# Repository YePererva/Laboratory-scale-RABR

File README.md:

# Laboratory scale RABR

This repository contains some developments on laboratory-scale Rotating Algal Biofilm Reactor (RABR).
The reactor were build for one of student-projects.

# Content

Folder `electronics` contains the schematics for two designed devices:
- Motor controller for there stepper motors as shaft drives for reactor
- Environment monitor for monitoring conditions of air and light around reactor. This monitor reads:
   - Temperature, Pressure and Relative Humidity of air (with conversion to absolute humidity)
   - Total flux, Photo-synthetically Active Radiation, UV flux.

Folder `models` contains the designer reactor for running in triplicate.

Folder `images` contains CAD renders and photos taken of working reactor and equipment.

# Used tools:
- KiCad : for schematics
- SolidWorks Educational : for designing the reactor

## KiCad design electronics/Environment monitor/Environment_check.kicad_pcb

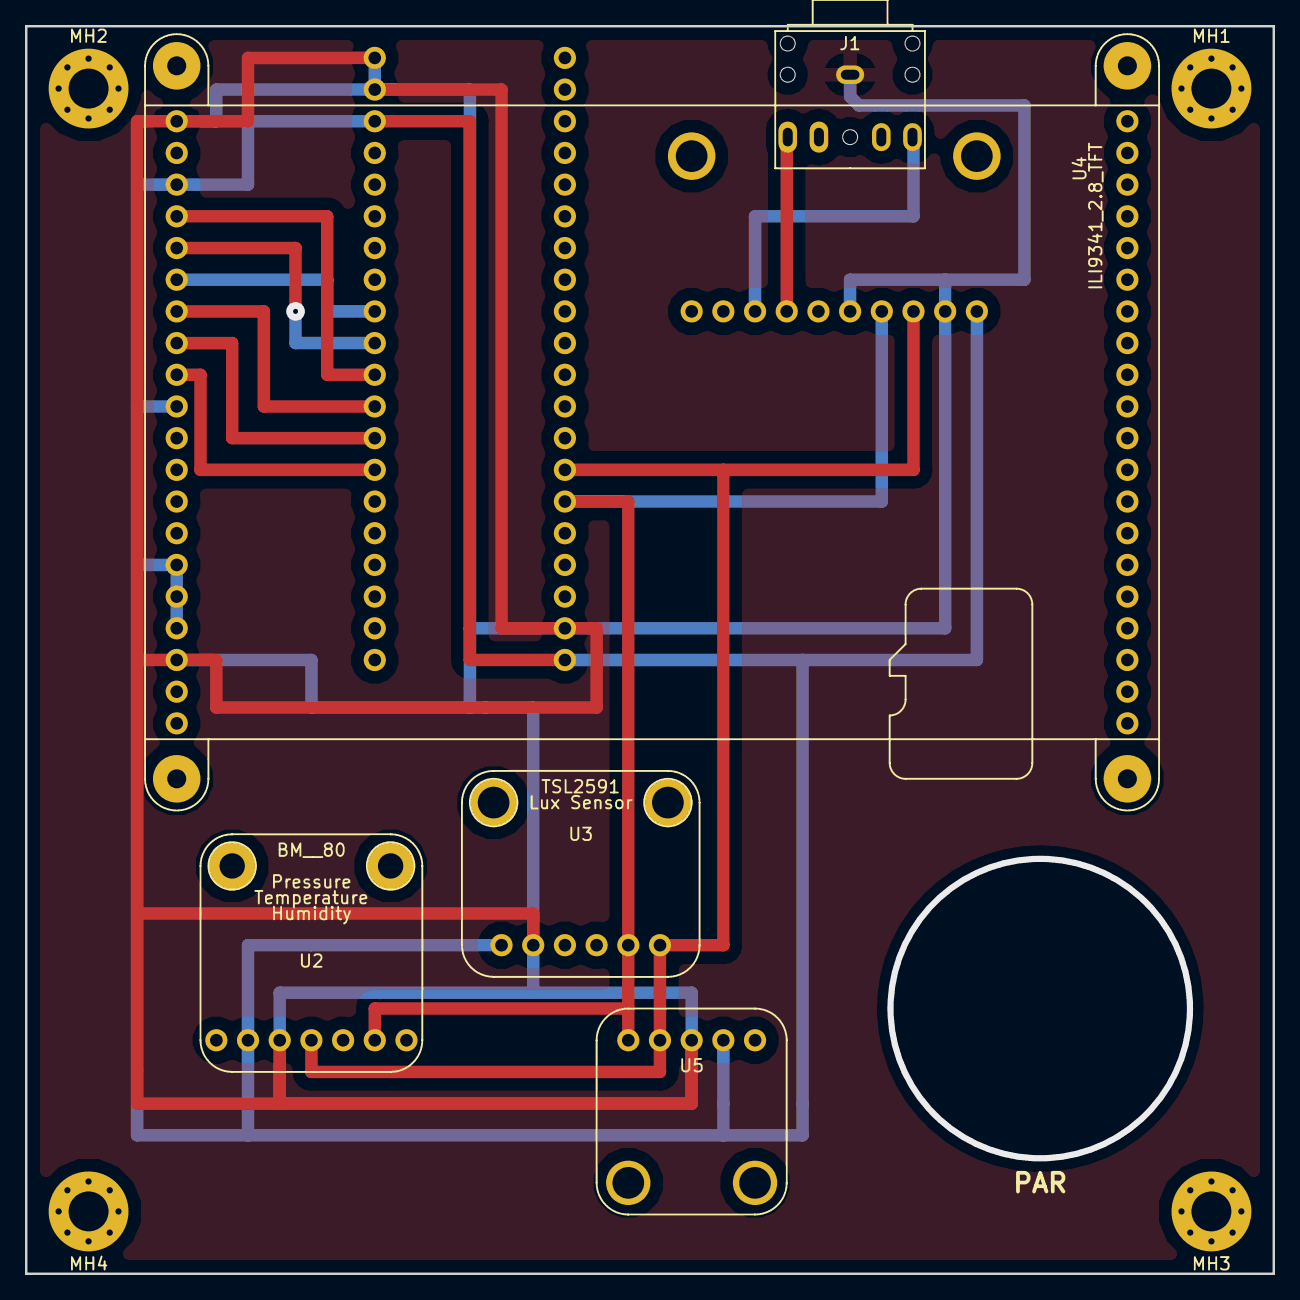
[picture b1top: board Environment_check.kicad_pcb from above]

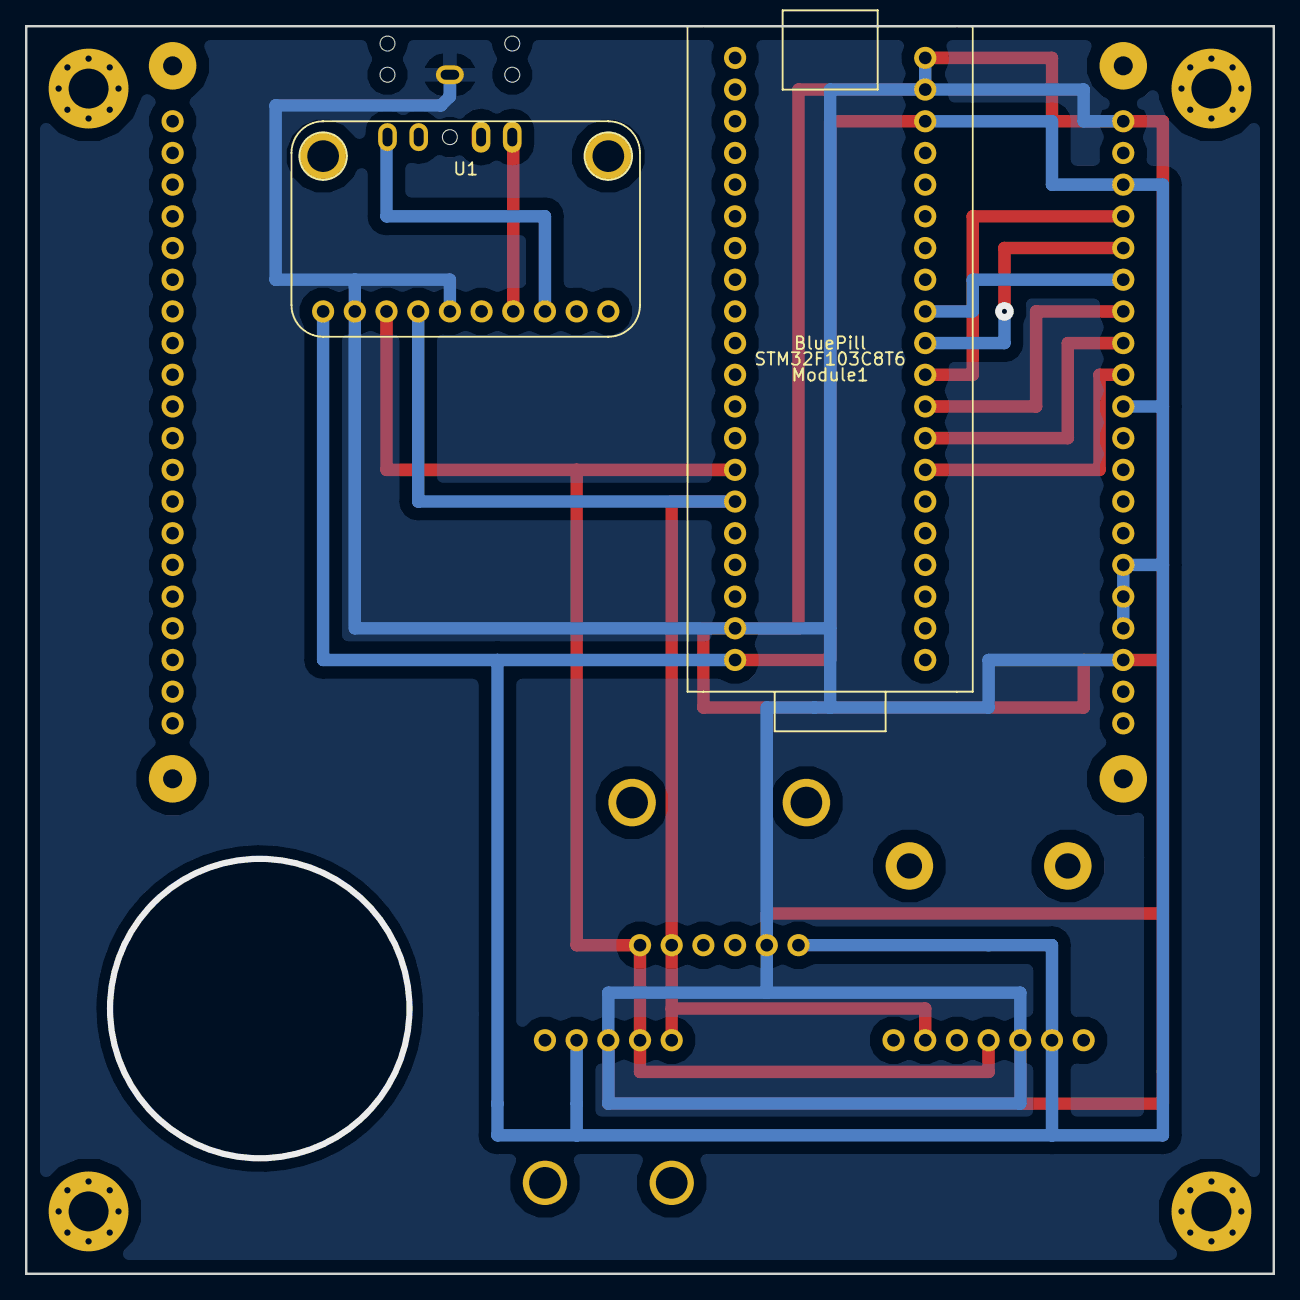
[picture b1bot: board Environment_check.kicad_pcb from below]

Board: 2 copper layers, 100.0 x 100.0 mm, 11 parts (2 on the bottom side), 12 nets.

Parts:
J1: Audio_3.5mm; Audio 3.5 Jack [4Ucon 08780]
MH1, MH2, MH3, MH4: MountingHole; MountingHole_3.2mm_M3_Pad_Via
Module1: BluePill
U1: ADS1115_ADS1015
U2: BM__80; BME280_BMP280_BME680
U3: TSL2591
U4: ILI9341_2.8_TFT; adafruit_ILI9341_2.8_double_mode
U5: VEML6075

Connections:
+3V3: Module1.20, Module1.38, U1.1, U2.2, U3.1, U4.23, U4.30, U4.35, U4.36, U4.37, U5.2
CLK: Module1.30, U4.24
ChipSelect: Module1.29, U4.27
Data_Command: Module1.28, U4.28
GND: J1.1, Module1.19, Module1.39, Module1.40, U1.2, U1.5, U2.3, U3.2, U4.21, U4.38, U5.3
MISO: Module1.31, U4.25
MOSI: Module1.32, U4.26
unnamed: J1.2, U1.8
unnamed: J1.5, U1.7
Reset: Module1.27, U4.29
SCL: Module1.14, U1.3, U2.4, U3.6, U5.4
SDA: Module1.15, U1.4, U2.6, U3.5, U5.5

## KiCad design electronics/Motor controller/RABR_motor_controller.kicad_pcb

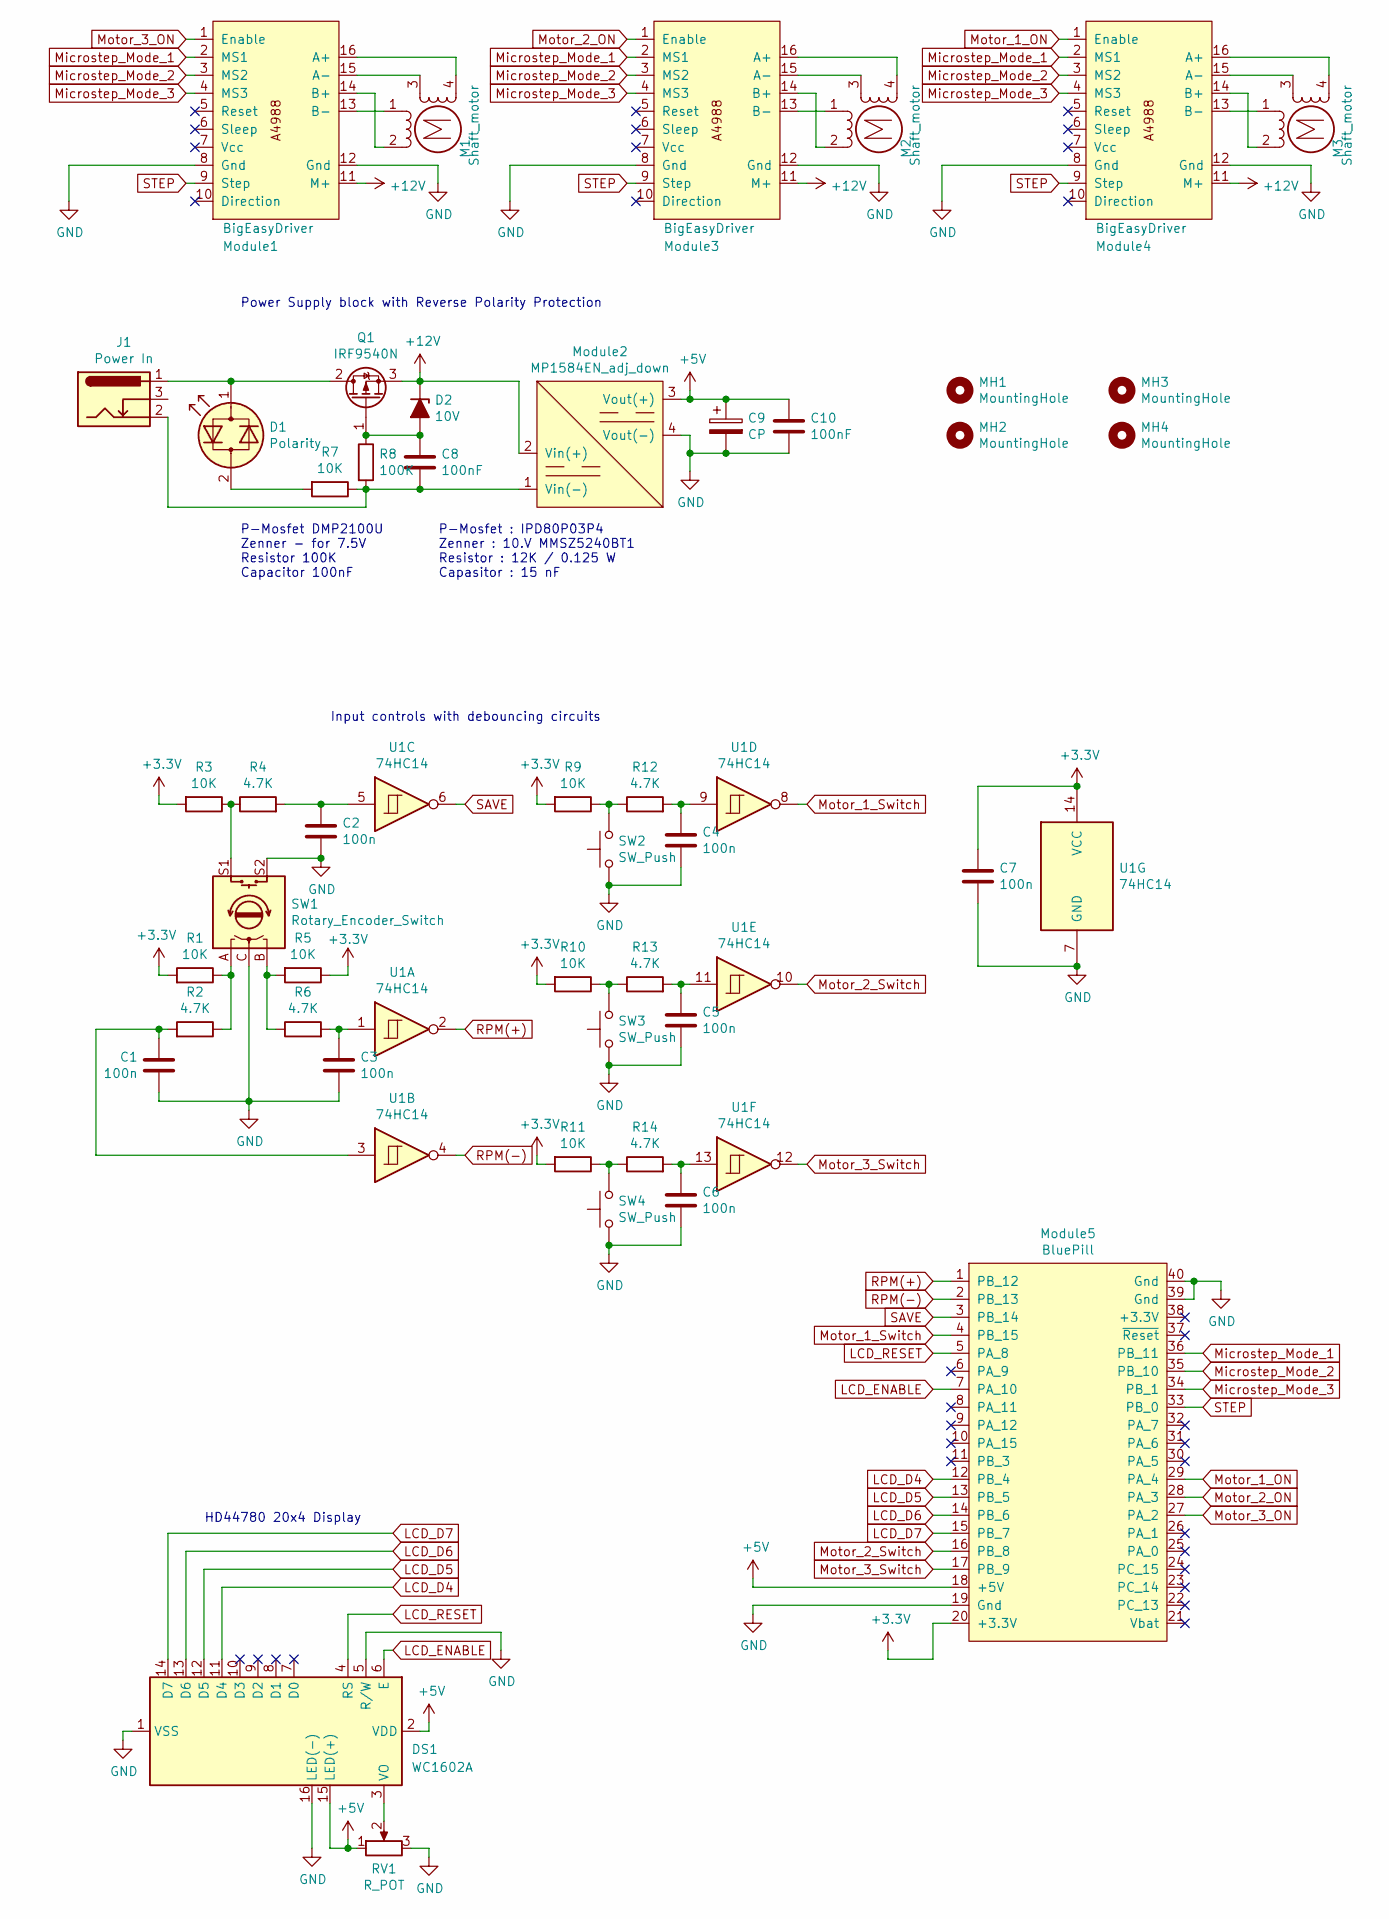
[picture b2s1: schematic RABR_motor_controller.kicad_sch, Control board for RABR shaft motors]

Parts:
C1, C2, C3, C4, C5, C6, C7: 100n; C_0805_2012Metric_Pad1.15x1.40mm_HandSolder
C8, C10: 100nF; C_0805_2012Metric_Pad1.15x1.40mm_HandSolder
C9: CP; CP_Elec_10x10
D1: Polarity; LED_D3.0mm_Clear
D2: 10V; D_DO-41_SOD81_P7.62mm_Horizontal
DS1: WC1602A
J1: Power In; BarrelJack_Horizontal
M1, M2, M3: Shaft_motor; TerminalBlock_Phoenix_MPT-0,5-4-2.54_1x04_P2.54mm_Horizontal
MH1, MH2, MH3, MH4: MountingHole; MountingHole_3.2mm_M3_DIN965_Pad
Module1, Module3, Module4: BigEasyDriver; BigEasyDriver_v1.6
Module2: MP1584EN_adj_down; MP1584_adj
Module5: BluePill
Q1: IRF9540N; TO-220-3_Vertical
R1, R3, R5, R7, R9, R10, R11: 10K; R_1206_3216Metric_Pad1.42x1.75mm_HandSolder
R2, R4, R6, R12, R13, R14: 4.7K; R_1206_3216Metric_Pad1.42x1.75mm_HandSolder
R8: 100K; R_1206_3216Metric_Pad1.42x1.75mm_HandSolder
RV1: R_POT; Potentiometer_Bourns_3386C_Horizontal
SW1: Rotary_Encoder_Switch; RotaryEncoder_Alps_EC12E-Switch_Vertical_H20mm
SW2, SW3, SW4: SW_Push; SW_PUSH_6mm_H8.5mm
U1: 74HC14; DIP-14_W7.62mm_LongPads

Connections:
+3V3: C7.1, Module5.20 (+3.3V), R1.2, R3.2, R5.1, R9.2, R10.2, R11.2, U1.14 (VCC)
+5V: C9.1, C10.1, DS1.2 (VDD), DS1.15 (LED(+)), Module2.3 (Vout(+)), Module5.18 (+5V), RV1.1
+12V: D2.1 (K), Module1.11 (M+), Module2.2 (Vin(+)), Module3.11 (M+), Module4.11 (M+), Q1.3 (S)
GND: C1.2, C2.2, C3.2, C4.2, C5.2, C6.2, C7.2, C9.2, C10.2, DS1.1 (VSS), DS1.5 (R/W), DS1.16 (LED(-)), Module1.8 (Gnd), Module1.12 (Gnd), Module2.4 (Vout(-)), Module3.8 (Gnd), Module3.12 (Gnd), Module4.8 (Gnd), Module4.12 (Gnd), Module5.19 (Gnd), Module5.39 (Gnd), Module5.40 (Gnd), RV1.3, SW1.C, SW1.S2, SW2.1, SW3.1, SW4.1, U1.7 (GND)
LCD_D4: DS1.11 (D4), Module5.12 (PB_4)
LCD_D5: DS1.12 (D5), Module5.13 (PB_5)
LCD_D6: DS1.13 (D6), Module5.14 (PB_6)
LCD_D7: DS1.14 (D7), Module5.15 (PB_7)
LCD_ENABLE: DS1.6 (E), Module5.7 (PA_10)
LCD_RESET: DS1.4 (RS), Module5.5 (PA_8)
Microstep_Mode_1: Module1.2 (MS1), Module3.2 (MS1), Module4.2 (MS1), Module5.36 (PB_11)
Microstep_Mode_2: Module1.3 (MS2), Module3.3 (MS2), Module4.3 (MS2), Module5.35 (PB_10)
Microstep_Mode_3: Module1.4 (MS3), Module3.4 (MS3), Module4.4 (MS3), Module5.34 (PB_1)
Motor_1_ON: Module4.1 (Enable), Module5.29 (PA_4)
Motor_1_Switch: Module5.4 (PB_15), U1.8
Motor_2_ON: Module3.1 (Enable), Module5.28 (PA_3)
Motor_2_Switch: Module5.16 (PB_8), U1.10
Motor_3_ON: Module1.1 (Enable), Module5.27 (PA_2)
Motor_3_Switch: Module5.17 (PB_9), U1.12
unnamed: C1.1, R2.2, U1.3
unnamed: C2.1, R4.2, U1.5
unnamed: C3.1, R6.2, U1.1
unnamed: C4.1, R12.2, U1.9
unnamed: C5.1, R13.2, U1.11
unnamed: C6.1, R14.2, U1.13
unnamed: C8.1, D2.2 (A), Q1.1 (G), R8.1
unnamed: C8.2, J1.2, Module2.1 (Vin(-)), R7.1, R8.2
unnamed: D1.1 (KA), J1.1, Q1.2 (D)
unnamed: D1.2 (AK), R7.2
unnamed: DS1.3 (VO), RV1.2
unnamed: M1.1, Module1.13 (B-)
unnamed: M1.2 (-), Module1.14 (B+)
unnamed: M1.3, Module1.15 (A-)
unnamed: M1.4, Module1.16 (A+)
unnamed: M2.1, Module3.13 (B-)
unnamed: M2.2 (-), Module3.14 (B+)
unnamed: M2.3, Module3.15 (A-)
unnamed: M2.4, Module3.16 (A+)
unnamed: M3.1, Module4.13 (B-)
unnamed: M3.2 (-), Module4.14 (B+)
unnamed: M3.3, Module4.15 (A-)
unnamed: M3.4, Module4.16 (A+)
unnamed: R1.1, R2.1, SW1.A
unnamed: R3.1, R4.1, SW1.S1
unnamed: R5.2, R6.1, SW1.B
unnamed: R10.1, R13.1, SW3.2
unnamed: R11.1, R14.1, SW4.2
unnamed: R9.1, R12.1, SW2.2
RPM(+): Module5.1 (PB_12), U1.2
RPM(-): Module5.2 (PB_13), U1.4
SAVE: Module5.3 (PB_14), U1.6
STEP: Module1.9 (Step), Module3.9 (Step), Module4.9 (Step), Module5.33 (PB_0)

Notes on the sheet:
HD44780 20x4 Display
Power Supply block with Reverse Polarity Protection
P-Mosfet DMP2100U Zenner - for 7.5V Resistor 100K Capacitor 100nF
Input controls with debouncing circuits
P-Mosfet : IPD80P03P4 Zenner : 10.V MMSZ5240BT1 Resistor : 12K / 0.125 W Capasitor : 15 nF

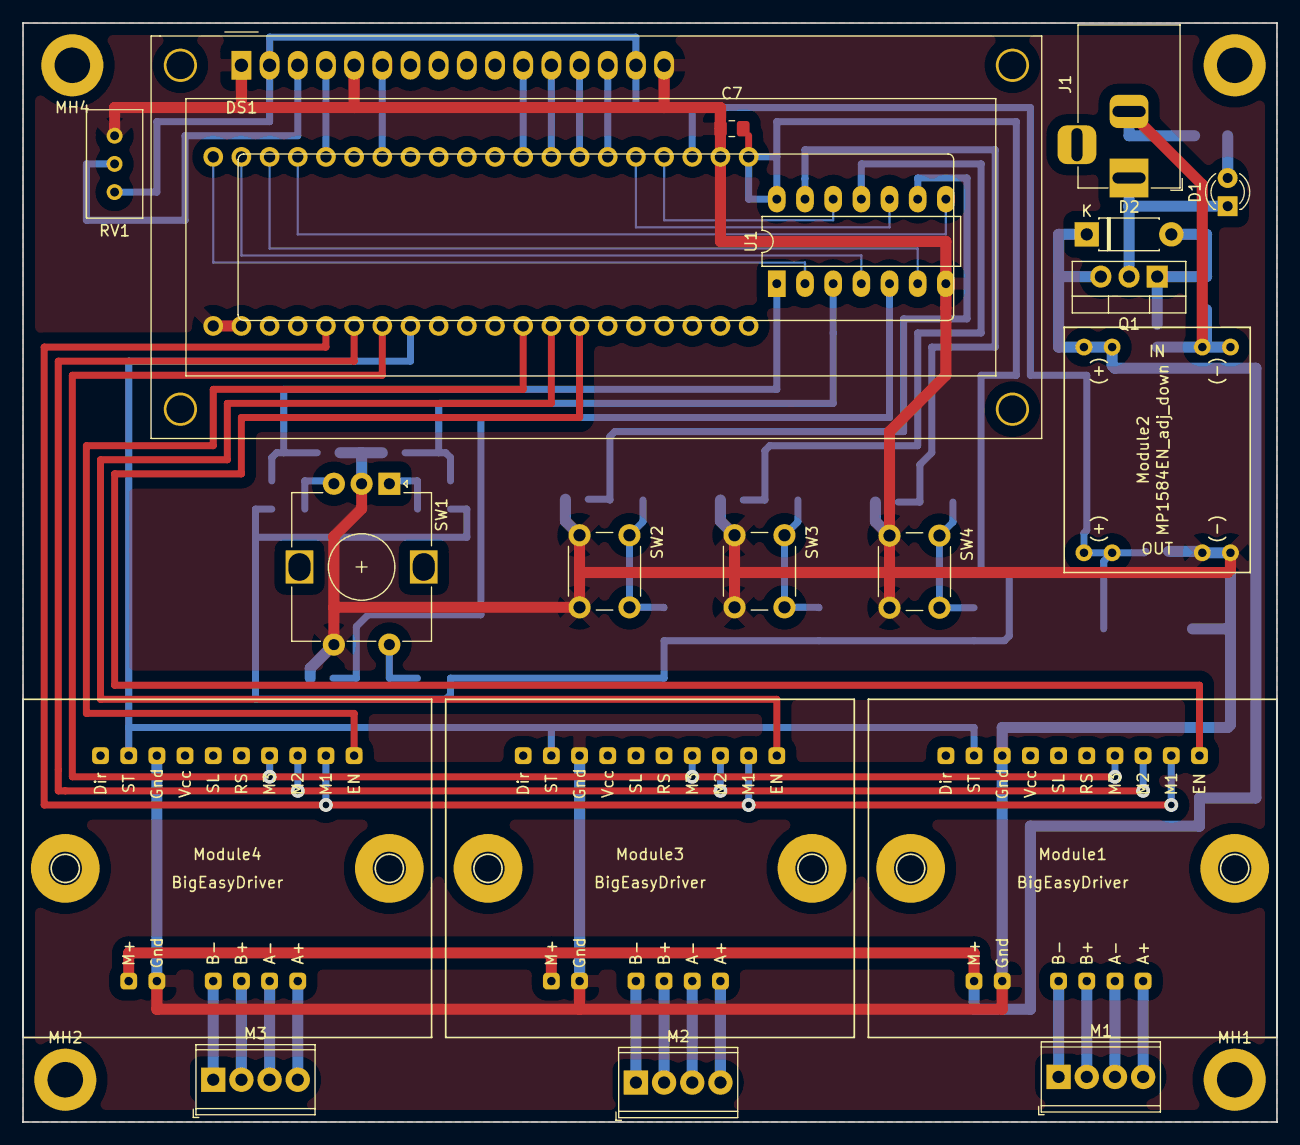
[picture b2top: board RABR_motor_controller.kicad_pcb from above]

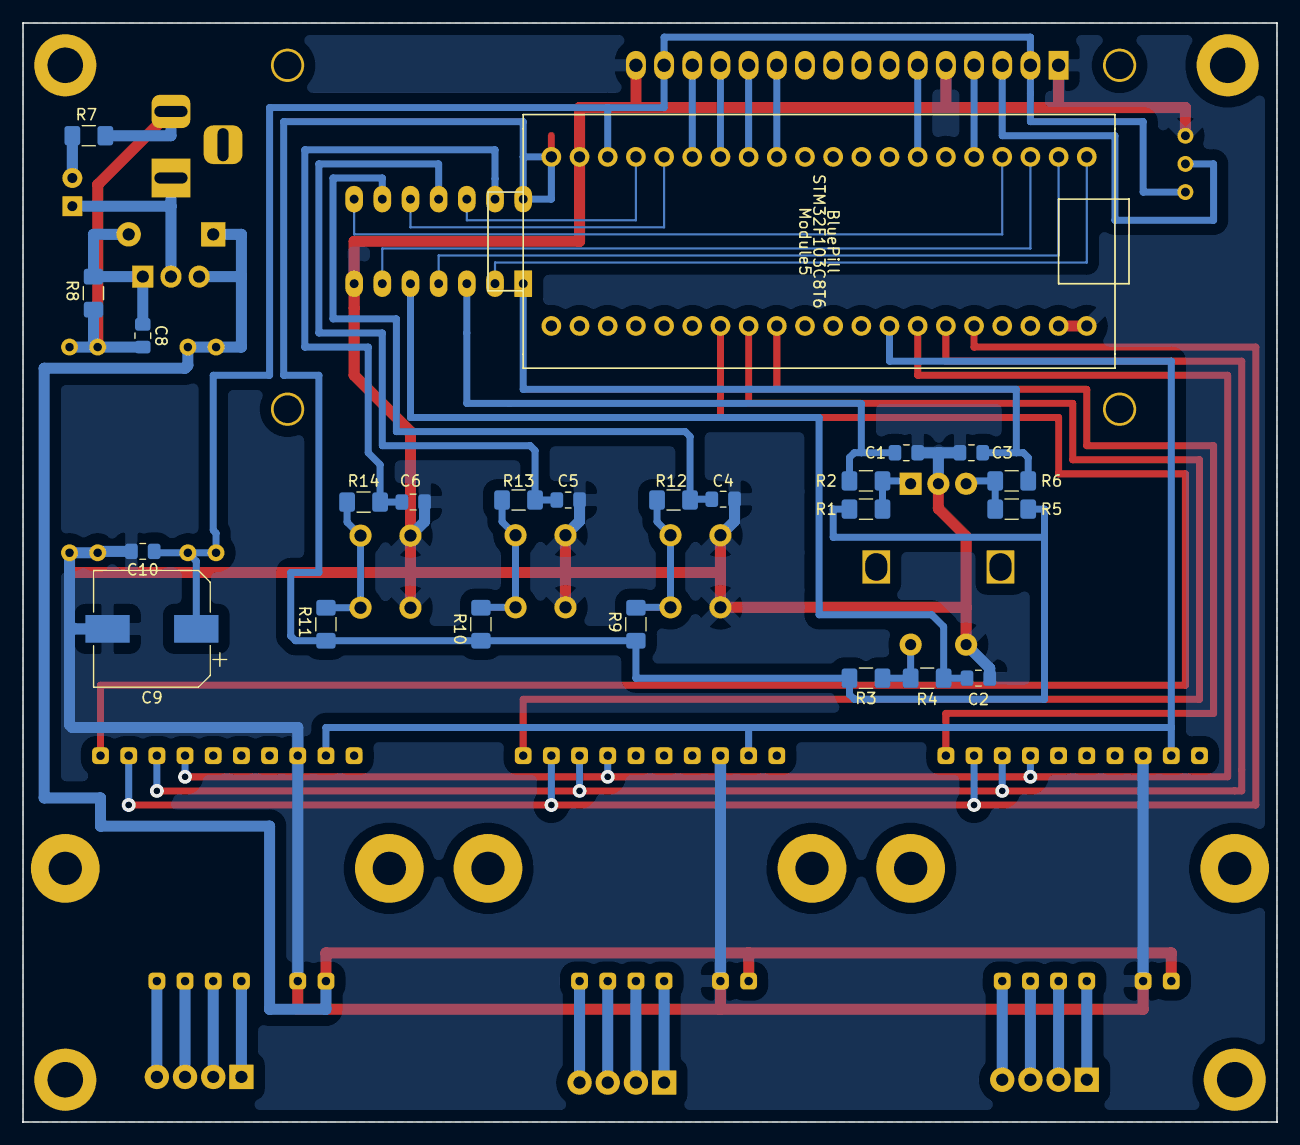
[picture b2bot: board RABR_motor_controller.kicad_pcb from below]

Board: 2 copper layers, 113.0 x 99.1 mm, 47 parts (24 on the bottom side), 52 nets.

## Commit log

2020-06-24 Main commit
    added main components:
    - schematics
    - models
2020-10-28 Purged ignored files
2021-06-29 Reopened with Kicad 5.99
